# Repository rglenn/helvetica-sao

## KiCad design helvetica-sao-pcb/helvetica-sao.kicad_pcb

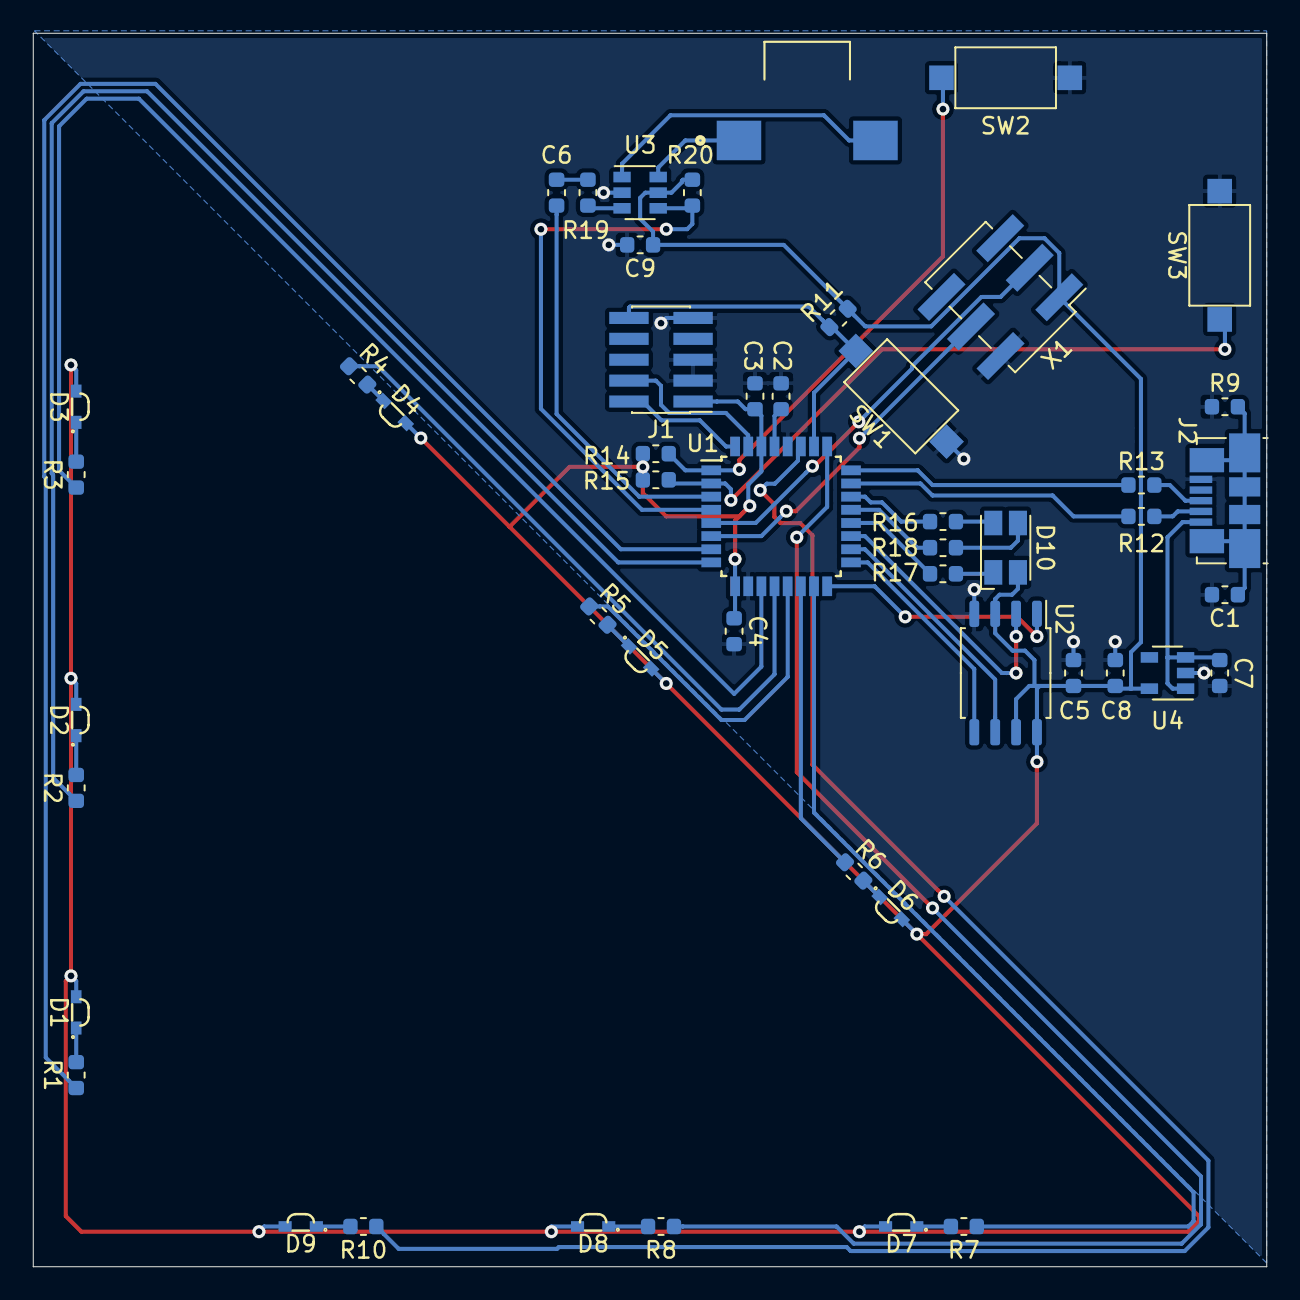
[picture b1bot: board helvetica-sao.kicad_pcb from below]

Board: 2 copper layers, 75.0 x 75.0 mm, 50 parts (50 on the bottom side), 50 nets.

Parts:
C1, C3, C5, C6: 100n; C_0603_1608Metric
C2, C4, C7, C8, C9: 1u; C_0603_1608Metric
D1, D2, D3, D4, D5, D6, D7, D8, D9: LED; LED_0802_SideEmitting
D10: LED_RGBA; LED_Avago_PLCC4_3.2x2.8mm_CW
J1: Conn_ARM_JTAG_SWD_10; PinHeader_2x05_P1.27mm_Vertical_SMD
J2: USB_B_Micro; USB_Micro-B_Molex_47346-0001
LS1: SMT-1127-S-R; XDCR_SMT-1127-S-R
R1, R2, R3, R4, R5, R6, R7, R8, R10, R16, R17, R18: 150; R_0603_1608Metric
R9: 1M; R_0603_1608Metric
R11, R14, R15, R20: 10K; R_0603_1608Metric
R12, R13: 22; R_0603_1608Metric
R19: 17K; R_0603_1608Metric
SW1, SW2, SW3: SW_Push; SW_SPST_CK_RS282G05A3
U1: ATSAMD21E1xA; LQFP-32_7x7mm_Pitch0.8mm
U2: W25Q32JVSS; SOIC-8_5.23x5.23mm_P1.27mm
U3: PAM8301; SOT-23-6
U4: MIC5504-3.3YM5; SOT-23-5
X1: Badgelife_sao_connector_v169bis; PinHeader_2x03_P2.54mm_Vertical_SMD

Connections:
+3V3: C3.1, C4.1, C5.1, C8.1, C9.1, D1.2, D2.2, D3.2, D4.2, D5.2, D6.2, D7.2, D8.2, D9.2, D10.4, J1.1, R11.2, R14.1, R15.1, R20.2, U1.9, U1.30, U2.3, U2.7, U2.8, U3.5, U4.5, X1.1
/BUTTON1: R14.2, SW2.1, U1.1
/BUTTON2: R15.2, SW3.1, U1.2
/FLASH_CLK: U1.18, U2.6
/FLASH_CS: U1.16, U2.1
/FLASH_MISO: U1.19, U2.2
/FLASH_MOSI: U1.17, U2.5
/LEDA: R1.1, U1.7
/LEDB: R2.1, U1.8
/LEDC: R3.1, U1.11
/LEDD: R4.1, U1.12
/LEDE: R5.1, U1.13
/LEDF: R6.1, U1.14
/LEDG: R7.1, U1.15
/LEDH: R8.1, U1.25
/LEDI: R10.1, U1.27
/SCL: U1.6, X1.4
/SDA: U1.5, X1.3
/SPEAKER: C6.2, U1.3
/SPEAKER_SD: R20.1, U1.4, U3.4
/STATUS_B: R18.2, U1.21
/STATUS_G: R16.2, U1.22
/STATUS_R: R17.2, U1.20
/SWCLK: J1.4, U1.31
/SWDIO: J1.2, U1.32
/VBUS: C7.1, J2.1, U4.1, U4.3
/~RESET: J1.10, R11.1, SW1.2, U1.26
GND: C1.2, C2.2, C3.2, C4.2, C5.2, C7.2, C8.2, C9.2, J1.3, J1.5, J1.9, J2.5, R9.1, SW1.1, SW2.2, SW3.2, U1.10, U1.28, U2.4, U3.2, U4.2, X1.2
unnamed: C1.1, J2.6, R9.2
unnamed: C2.1, U1.29
unnamed: C6.1, R19.1
unnamed: D1.1, R1.2
unnamed: D2.1, R2.2
unnamed: D3.1, R3.2
unnamed: D4.1, R4.2
unnamed: D5.1, R5.2
unnamed: D6.1, R6.2
unnamed: D7.1, R7.2
unnamed: D8.1, R8.2
unnamed: D9.1, R10.2
unnamed: D10.1, R17.1
unnamed: D10.2, R16.1
unnamed: D10.3, R18.1
unnamed: J2.2, R12.2
unnamed: J2.3, R13.2
unnamed: LS1.1, U3.6
unnamed: LS1.2, U3.1
unnamed: R12.1, U1.23
unnamed: R13.1, U1.24
unnamed: R19.2, U3.3

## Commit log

2019-11-16 Adding ALL THE FILES
